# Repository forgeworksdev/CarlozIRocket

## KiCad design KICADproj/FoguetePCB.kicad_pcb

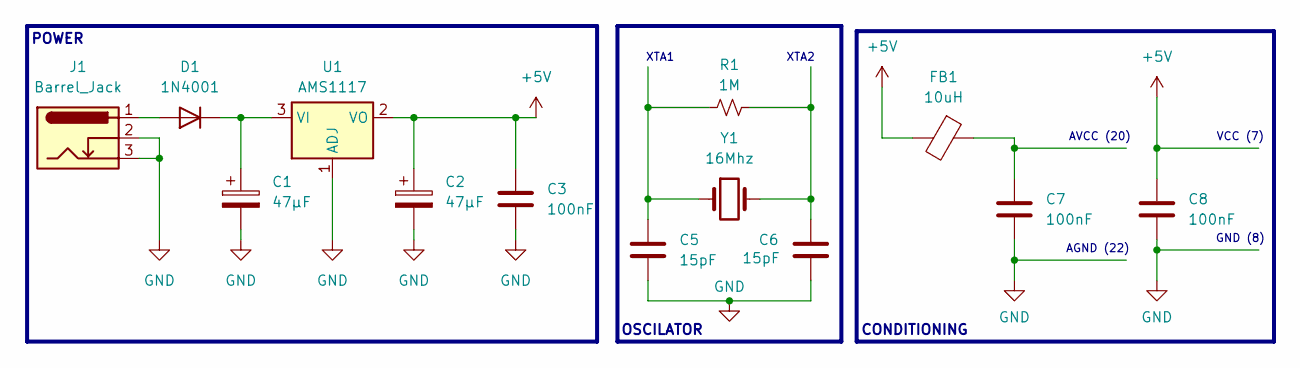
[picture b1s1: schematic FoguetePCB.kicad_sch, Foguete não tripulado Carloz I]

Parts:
C1, C2: 47μF; CP_Radial_D8.0mm_P2.50mm
C3, C7, C8: 100nF; C_Disc_D3.0mm_W1.6mm_P2.50mm
C5, C6: 15pF; C_Disc_D3.0mm_W1.6mm_P2.50mm
D1: 1N4001; D_DO-41_SOD81_P10.16mm_Horizontal
FB1: 10uH
J1: Barrel_Jack; JackP4-54-00166
R1: 1M; R_Axial_DIN0204_L3.6mm_D1.6mm_P1.90mm_Vertical
U1: AMS1117; SOT-223-3_TabPin2
Y1: 16Mhz; Crystal_HC49-4H_Vertical

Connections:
+5V: C2.1, C3.1, C8.1, FB1.2, U1.2 (VO)
GND: C1.2, C2.2, C3.2, C5.2, C6.2, C7.2, C8.2, J1.2, J1.3, U1.1 (ADJ)
unnamed: C5.1, R1.1, Y1.1
unnamed: C6.1, R1.2, Y1.2
unnamed: C7.1, FB1.1
unnamed: D1.2 (A), J1.1
unnamed: C1.1, D1.1 (K), U1.3 (VI)

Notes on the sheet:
OSCILATOR
GND (8)
AGND (22)
VCC (7)
XTA1
POWER
AVCC (20)
CONDITIONING
XTA2

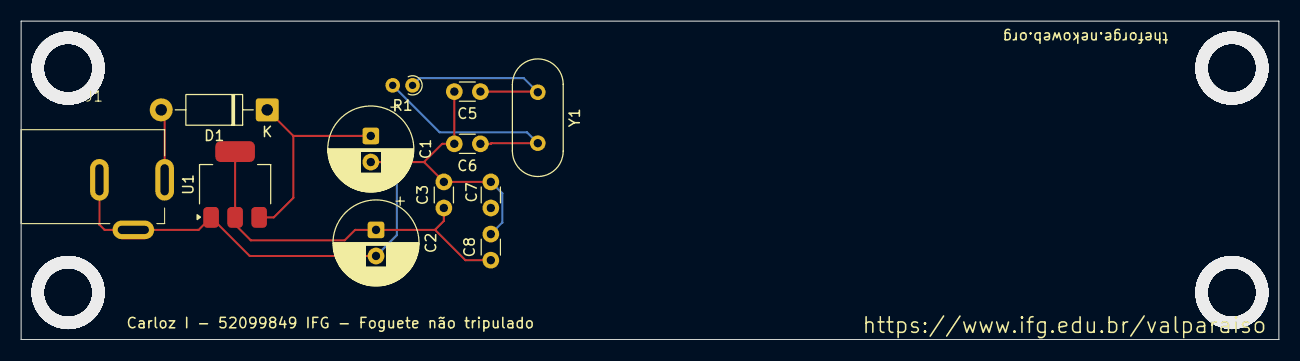
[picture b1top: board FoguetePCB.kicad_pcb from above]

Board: 2 copper layers, 120.5 x 30.5 mm, 12 parts (0 on the bottom side), 6 nets.

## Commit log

2026-02-11 Upload files
2026-06-08 Renamed files, add license.txt
2026-06-08 Update license to CC BY-NC.
